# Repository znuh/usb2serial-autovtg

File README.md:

# USB2serial-AutoVtg
<br>
USB to serial adapter with automatic target voltage detection, buffered IOs, 1.8V to 5V support and backflow current protection

## Why yet another USB to serial adapter?
This adapter adds several **convenience & protection features** most existing adapters do not have.

I'll use an analogy to explain this: For voltage measurements you can either use a naked analog-to-digital converter (ADC) or a digital multimeter/oscilloscope.
Digital multimeters/oscilloscopes have analog frontends to support different voltage ranges and take a bit of abuse (i.e. overvoltage, etc.) with no permanent damage, while an ADC by itself does not have these features.  
When it comes to USB to serial converters the situation is similar. The converter chip by itself usually doesn't support multiple voltage ranges and can be damaged by overvoltage and overcurrent.

However, an even bigger problem is that adapters can also damage the target system when set to the wrong voltage, or through **backflow current** when connected to an unpowered target. (See [below](#backflow_current) for a detailed explanation.)  
To address these issues, this adapter uses **[buffered IOs](#backflow_current)** with backflow current protection and **[automatic target voltage detection](autovtg)**.

## Adapter Specifications
<table class="table table-striped">
  <tbody class="table-group-divider">
    <tr>
      <td class="td1">IC:</td>
      <td><a href="https://ftdichip.com/products/ft234xd/">FTDI FT234XD</a></td>
    </tr>
    <tr>
      <td class="td1">Signals:</td>
      <td>GND, Rx, Tx, (Vtg - optional Vtarget reference voltage input)</td>
    </tr>
    <tr>
      <td class="td1">IO Voltage:</td>
      <td>1.8V - 5V (automatic detection or via reference pin)</td>
    </tr>
    <tr>
      <td class="td1">Baudrates:</td>
      <td>
		  <ul>
		  <li>4800 Baud - 250kBaud with <a href="#autovtg" class="link-primary">automatic target voltage detection</a></li>
		  <li>300 Baud - 3MBaud with target voltage provided through Vtg pin</li>
		  </ul>
      </td>
    </tr>
    <tr>
      <td class="td1">Buffered IOs:</td>
      <td><a href="https://assets.nexperia.com/documents/data-sheet/74LVC1G17.pdf">74LVC1G17</a> Buffers<br>
      These buffers prevent <a href="#backflow_current" class="link-primary">potentially damaging backflow current</a> when only the target <b>or</b> the USB to Serial Adapter is powered.
      </td>
    </tr>
    <tr>
      <td class="td1">IO Protection:</td>
      <td>120Ω series resistors on Rx/Tx.<br>
      These resistors protect both the USB to Serial Adapter and the target by limiting the short-circuit current 
      when the adapter is connected to the target incorrectly (e.g. adapter Tx connected to target Tx).<br>
      Current limits:
      <ul>
      <li>@1.8V: &lt;15mA</li>
      <li>@3.3V: &lt;28mA</li>
      <li>@5V: &lt;42mA</li>
      </ul>
      </td>
    </tr>
    <tr>
      <td class="td1">Connector:</td>
      <td>USB-C</td>
    </tr>
    <tr>
      <td class="td1">LED:</td>
      <td>Rx/Tx (single LED for both)</td>
    </tr>
</tbody>
</table>

## What is backflow current protection?
The most common USB to Serial Adapters have unbuffered IOs. This means the in- and outputs of the converter IC are
directly connected to the target. When such an adapter is not connected to USB, but to a powered target, current flows
from the output of the target into the input of the converter IC and to Vdd through the 
<a href="https://electronics.stackexchange.com/questions/179450/power-and-ground-clamp-diodes-in-cmos-io-buffer">
clamping diode</a>.  

The same problem occurs when the USB to Serial Adapter is connected to USB and an unpowered target. Current from the
converter output flows into the target input and to Vdd of the target through the input clamping diode.
This penomenon is called
<a href="https://e2e.ti.com/blogs_/b/analogwire/posts/back-powering-why-are-the-lights-on-when-the-power-is-off">
back powering</a>.

Backflow current often exceeds the maximum ratings of the ICs involved. This can permanently damage both the 
(expensive) target and the USB to Serial Adapter. Modern 1.8V devices are more prone to permanent damage through
backflow current because their IOs are significantly less robust than old 5V IOs.<br>
Suitable IO buffers (such as the <a href="https://assets.nexperia.com/documents/data-sheet/74LVC1G17.pdf">74LVC1G17</a>)
prevent this by limiting the backflow current to a few µA.
With these buffers having an unpowered adapter connected to a powered board - and vice versa - no longer poses a risk.

## How does the automatic target voltage detection work?
Connecting a 3.3V USB to Serial Adapter to a 1.8V target (or a 5V adapter to a 3.3V target) can permanently damage
the target, because the excessive voltage can result in a high current through the clamping diode and an overvoltage
on the Vdd supply of the target.

Therefore buffered USB to Serial Adapters usually have a Vtarget (or Vtg/Vref) sense input for the target IO voltage.
The sense input is used to match the IO voltage of the adapter to the target.
This adapter also has such a Vtarget sense input, but in most cases connecting it is optional, because the adapter
can <b>detect the target IO voltage automatically</b> by deriving it from the target Tx signal.

This is done with a <a href="https://www.analog.com/en/technical-articles/ltc6244-high-speed-peak-detector.html">
peak detector circuit</a> based on a common Operational Amplifier (a <a href="https://www.ti.com/product/LMV358A">LMV358A</a>). The automatic detection is designed to work with baud rates ranging from 4800 Baud up to 250kBaud.
For lower or higher baudrates (and for unidirectional use-cases where the target does not have a Tx signal) 
a regular Vtarget sense pin is also available.

The following oscilloscope screenshots show the target TX signal (red) and the recovered IO voltage (blue) at 115.2kBaud and 1.8V. The target is sending 0x00 bytes only - the positive startbits are sufficient to recover the IO voltage.  
  
Target IO voltage is detected shortly after the first startbit is sent.

When the target TX signal stays at 0V for a few milliseconds (target is powered off or transmitter shutdown), the recovered IO voltage also drops down to zero.

(115.2kBaud / 5V measurements can be found [here](https://github.com/znuh/usb2serial-autovtg/issues/2#issuecomment-1837257313).)

# License
Designed by Benedikt Heinz &lt;hunz at mailbox.org&gt;

Creative Commons Attribution/Share-Alike, all text above must be included in any redistribution. See license.txt for additional details.

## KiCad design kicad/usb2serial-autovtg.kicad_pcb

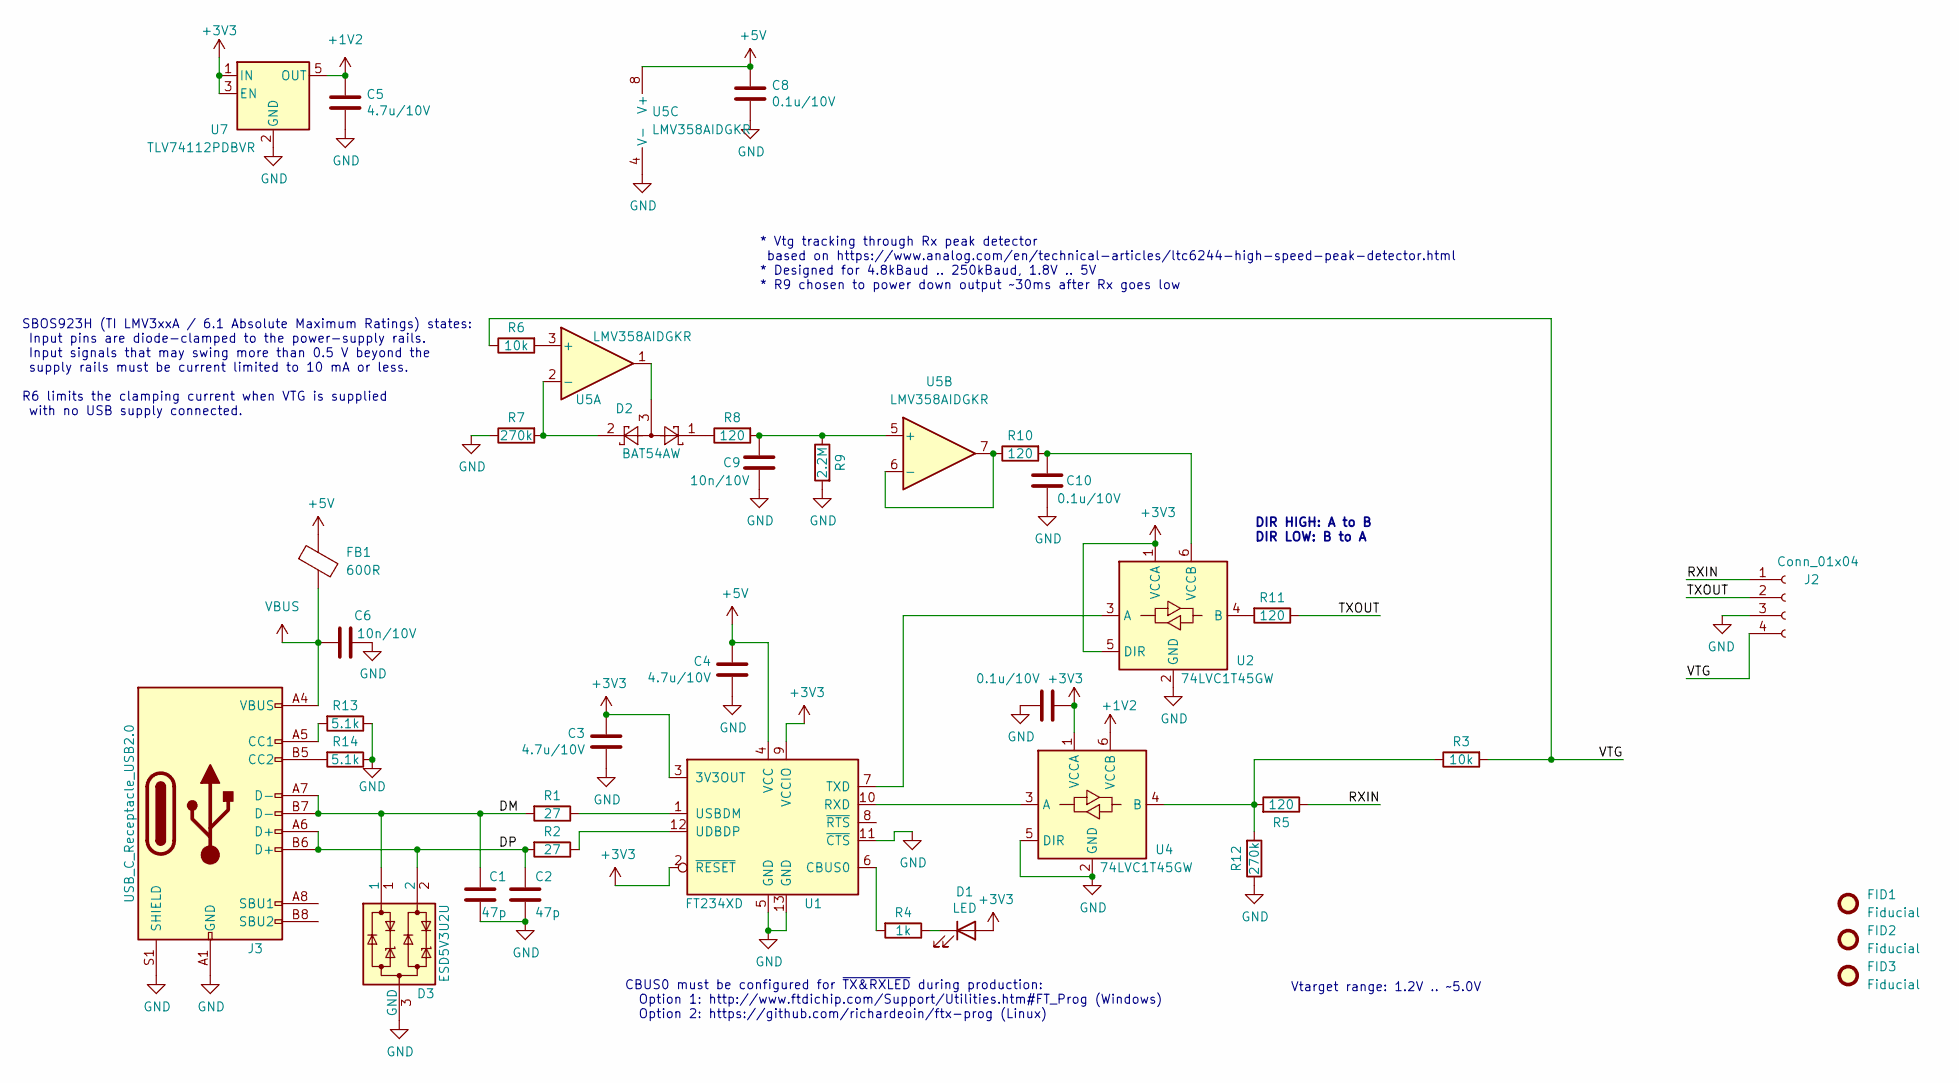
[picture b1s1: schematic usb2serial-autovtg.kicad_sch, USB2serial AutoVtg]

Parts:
C1, C2: 47p; C_0402_1005Metric
C3, C4, C5: 4.7u/10V; C_0402_1005Metric
C6, C9: 10n/10V; C_0402_1005Metric
C7, C8, C10: 0.1u/10V; C_0402_1005Metric
D1: LED; LED_0603_1608Metric
D2: BAT54AW; SOT-323_SC-70
D3: ESD5V3U2U; Infineon_PG-TSFP-3-1
FB1: 600R; L_0603_1608Metric
FID1, FID2, FID3: Fiducial; Fiducial_0.5mm_Mask1mm
J2: Conn_01x04; PinHeader_1x04_P2.54mm_Vertical
J3: USB_C_Receptacle_USB2.0; USB_C_Receptacle_GCT_USB4105-xx-A_16P_TopMnt_Horizontal
R1, R2: 27; R_0402_1005Metric
R3, R6: 10k; R_0402_1005Metric
R4: 1k; R_0402_1005Metric
R5, R8, R10, R11: 120; R_0402_1005Metric
R7, R12: 270k; R_0402_1005Metric
R9: 2.2M; R_0402_1005Metric
R13, R14: 5.1k; R_0402_1005Metric
U1: FT234XD; DFN-12-1EP_3x3mm_P0.45mm_EP1.66x2.38mm
U2, U4: 74LVC1T45GW; SOT-363_SC-70-6
U5: LMV358AIDGKR; VSSOP-8_3.0x3.0mm_P0.65mm
U7: TLV74112PDBVR; SOT-23-5

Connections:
+1V2: C5.1, U4.6 (VCCB), U7.5 (OUT)
+3V3: C3.1, C7.1, D1.2 (A), U1.2 (~RESET), U1.3 (3V3OUT), U1.9 (VCCIO), U2.1 (VCCA), U2.5 (DIR), U4.1 (VCCA), U7.1 (IN), U7.3 (EN)
+5V: C4.1, C8.1, FB1.1, U1.4 (VCC), U5.8 (V+)
/DM: C1.1, D3.1, J3.A7 (D-), J3.B7 (D-), R1.2
/DP: C2.1, D3.2, J3.A6 (D+), J3.B6 (D+), R2.2
/RXIN: J2.1, R5.1
/TXOUT: J2.2, R11.1
/VTG: J2.4, R3.2, R6.1
GND: C1.2, C2.2, C3.2, C4.2, C5.2, C6.2, C7.2, C8.2, C9.2, C10.2, D3.3 (GND), J2.3, J3.A1 (GND), J3.A12 (GND), J3.B1 (GND), J3.B12 (GND), J3.S1 (SHIELD), R7.1, R9.2, R12.1, R13.1, R14.1, U1.5 (GND), U1.11 (~CTS), U1.13 (GND), U2.2 (GND), U4.2 (GND), U4.5 (DIR), U5.4 (V-), U7.2 (GND)
unnamed: D1.1 (K), R4.1
unnamed: D2.1, R8.1
unnamed: D2.3, U5.1
unnamed: J3.A5 (CC1), R13.2
unnamed: J3.B5 (CC2), R14.2
unnamed: R4.2, U1.6 (CBUS0)
unnamed: U1.10 (RXD), U4.3 (A)
unnamed: U1.7 (TXD), U2.3 (A)
unnamed: R2.1, U1.12 (UDBDP)
unnamed: R1.1, U1.1 (USBDM)
unnamed: R11.2, U2.4 (B)
unnamed: C10.1, R10.2, U2.6 (VCCB)
unnamed: R3.1, R5.2, R12.2, U4.4 (B)
unnamed: R6.2, U5.3 (+)
unnamed: D2.2, R7.2, U5.2 (-)
unnamed: C9.1, R8.2, R9.1, U5.5 (+)
unnamed: R10.1, U5.6 (-), U5.7
VBUS: C6.1, FB1.2, J3.A4 (VBUS), J3.A9 (VBUS), J3.B4 (VBUS), J3.B9 (VBUS)

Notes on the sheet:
DIR HIGH: A to B DIR LOW: B to A
CBUS0 must be configured for ~{TX&RXLED} during production: Option 1: http://www.ftdichip.com/Support/Utilities.htm#FT_Prog (Windows) Option 2: https://github.com/richardeoin/ftx-prog (Linux)
SBOS923H (TI LMV3xxA / 6.1 Absolute Maximum Ratings) states: Input pins are diode-clamped to the power-supply rails. Input signals that may swing more than 0.5 V beyond the supply rails must be current limited to 10 mA or less. R6 limits the clamping current when VTG is supplied with no USB supply 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
* Vtg tracking through Rx peak detector based on https://www.analog.com/en/technical-articles/ltc6244-high-speed-peak-detector.html * Designed for 4.8kBaud .. 250kBaud, 1.8V .. 5V * R9 chosen to power down output ~30ms after Rx goes low
Vtarget range: 1.2V .. ~5.0V

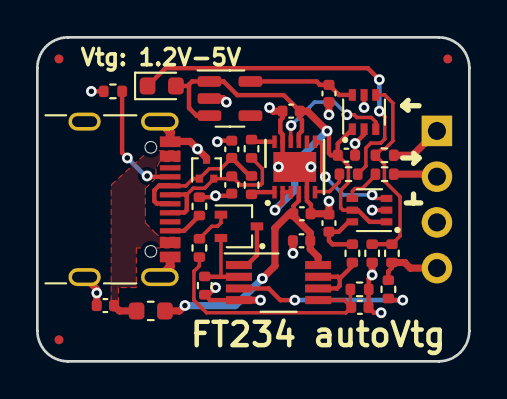
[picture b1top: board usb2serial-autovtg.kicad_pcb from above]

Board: 2 copper layers, 24.0 x 18.0 mm, 38 parts (0 on the bottom side), 27 nets.

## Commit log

2023-10-30 add license
2023-10-30 fix README.md
2023-10-30 initial import
2023-11-14 adding LTspice files
2023-11-14 add script for models download
2023-11-29 Update README.md - WIP
2023-11-30 Update README.md - fix typo
2024-01-14 1.2V: wip
2024-01-23 add note regarding DIR pin
2024-01-23 finalize rev3
2024-01-23 modify Vtg silkscreen text
2024-01-24 update ibom too
2024-02-08 add ftx-prog command

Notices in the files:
kicad/usb2serial-autovtg.kicad_sch:
https://creativecommons.org/licenses/by-sa/4.0/deed.en
License: Creative Commons Attribution/Share-Alike 4.0
